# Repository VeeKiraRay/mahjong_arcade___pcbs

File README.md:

# Mahjong arcade DIY control panels
Kicad projects for a small mahjong control panel pcb that can be wired to be used with a real arcade game

Inspired by buffis JammaMahjongAdapter
https://github.com/buffis/JammaMahjongAdapter

Mahjong pinout that was followed when designing these

Comparison with different versions next to "Hot Gimmick 3" arcade pcb. Added a commercial version for Windows as a size comparison as well. 

Ready to play with small control panel and mahjong to jamma adapter

## Mahjong control panel symbols
For printing stickers or otherwise marking control panels here are some of the common characters to use

Lower part of control panel
- coin (F.F.) / ko-i-n / コイン
- start / su-ta-a-to / スタート 
- bet / be-t-to / ベット
- take score / te-i-ku-su-ko / テイクスコアー
- double up (WUP) / da-bu-ru a-p-pu / ダブルアップ  
- big / bi-g-gu / ビッグ
- small / su-mo-ru / スモール
- last chance / ra-su-to ch-a-n-su / ラストチャンス
- kan / ka-n / カン
- pon / po-n / ポン
- chi / ch-i / チー
- riichi / ri-i-chi / リーチ
- ron / ro-n / ロン

Character suite to number conversion
- 1 / 一
- 2 / 二
- 3 / 三
- 4 / 四
- 5 / 五
- 6 / 六
- 7 / 七
- 8 / 八
- 9 / 九

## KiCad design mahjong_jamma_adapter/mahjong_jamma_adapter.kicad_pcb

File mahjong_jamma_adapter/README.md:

# Mahjong to JAMMA adapter

Enables you to play Mahjong games in a JAMMA setup like arcade cabinet or supergun. 
This has 3.96mm pitch for the mahjong side pads which is same as with JAMMA. Note that some Mahjong games use 4mm pitch.
Be sure to check that the adapter lines with the game pcb pads correctly.

The main Mahjong controls can be extended with the 6- and 5-pin connectors. 
Additional 4-pin connector is also available for wiring coin, test and service buttons with GND.
Connector pins are with 2.5mm pitch, but 2.54mm should also work.

The -5V requirement and GND to "JAMMA Spk-" can be bridged if needed.

Audio section can be wired with a switch to change between connecting "JAMMA Spk-" to "Mahjong Spk-" or to GND.
Be sure what connections your game(s) require. For example Hot Gimmick needs the "JAMMA Spk-" to be connected to "Mahjong Spk-" or there won't be any sound.
Connecting this wrong can cause sound to be missing, distorted, low volume and possibly components overheating.

Mahjong pinout that was followed when designing this

Bare pcb

Control panel poulated

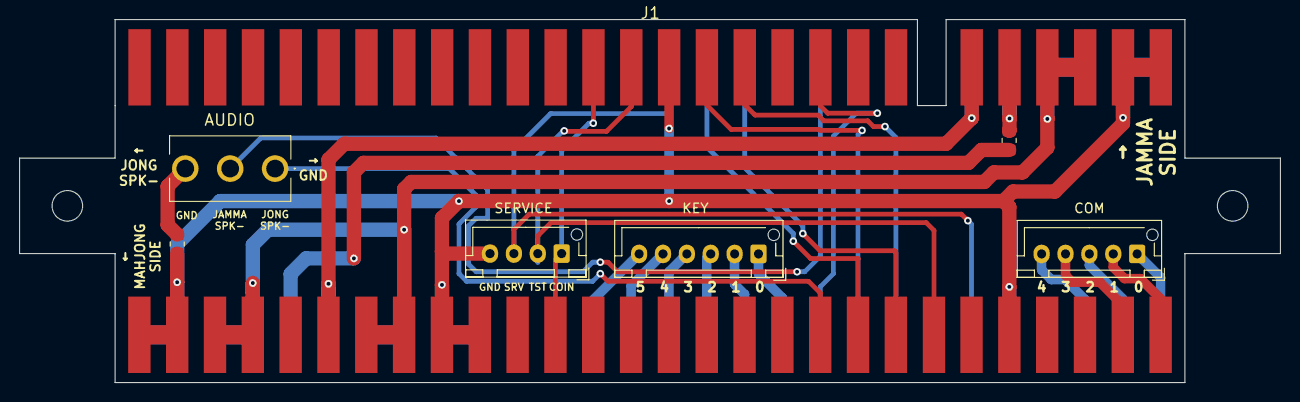
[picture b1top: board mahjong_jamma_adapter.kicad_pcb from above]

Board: 2 copper layers, 132.0 x 38.0 mm, 8 parts (0 on the bottom side), 27 nets.

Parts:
AUDIO: Mahjong_Connector; MAHJONG-56
COM: Conn_01x05; JST_XH_B5B-XH-AM_1x05_P2.50mm_Vertical
J1: Jamma_Connector; JAMMA-56
JMP1, JMP2: SolderJumper_2_Open; R_0805_2012Metric_Pad1.20x1.40mm_HandSolder
KEY: Conn_01x06; JST_XH_B6B-XH-AM_1x06_P2.50mm_Vertical
SERVICE: Conn_01x04; JST_XH_B4B-XH-AM_1x04_P2.50mm_Vertical
SW1: SW_SPDT; A101SYCQ04

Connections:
5V: AUDIO.21, AUDIO.22, AUDIO.25, AUDIO.26, AUDIO.Y, AUDIO.Z, AUDIO.c, AUDIO.d, J1.3, J1.4, J1.C, J1.D
12V: AUDIO.23, AUDIO.a, J1.6, J1.F
-5V: J1.5, J1.E, JMP1.2 (B)
-5V_M: AUDIO.b, JMP1.1 (A)
BLUE: AUDIO.K, J1.13
COIN: AUDIO.17, J1.16, SERVICE.1
COM0-3: AUDIO.A, COM.1
COM1-2: AUDIO.1, COM.2
COM2-6: AUDIO.B, COM.3
COM3-10: AUDIO.2, COM.4
COM4-7: AUDIO.C, COM.5
GND: AUDIO.5, AUDIO.19, AUDIO.20, AUDIO.27, AUDIO.28, AUDIO.E, AUDIO.W, AUDIO.X, AUDIO.e, AUDIO.f, J1.1, J1.2, J1.14, J1.A, J1.B, JMP2.2 (B), SERVICE.4
GREEN: AUDIO.8, J1.N
JAMMA_SPK-: J1.L, SW1.2 (B)
JONG_SPK-: AUDIO.10, SW1.1 (A)
KEY0-4: AUDIO.M, KEY.1
KEY1-5: AUDIO.N, KEY.2
KEY2-8: AUDIO.P, KEY.3
KEY3-9: AUDIO.R, KEY.4
KEY4-11: AUDIO.S, KEY.5
KEY5-1: AUDIO.T, KEY.6
unnamed: JMP2.1 (A), SW1.3 (C)
RED: AUDIO.J, J1.12
SERVICE: AUDIO.F, J1.R, SERVICE.3
SPK+: AUDIO.L, J1.10
SYNC: AUDIO.9, J1.P
TEST: AUDIO.7, J1.15, SERVICE.2

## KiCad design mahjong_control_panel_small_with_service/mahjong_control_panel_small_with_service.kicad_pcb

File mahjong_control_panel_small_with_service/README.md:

# Mahjong control panel small with service buttons

Smaller version of control panel with basic inputs and additional buttons for easy coin in, test for menus and service for alternative coin in and options.

- Connectors are with 2.5mm pitch, but 2.54mm should also work
- All buttons are 6mm. Any correct size button should work with or without the hats.
- Holes at the edge are M3 for attaching legs or to a case.

Bare pcb

Control panel poulated

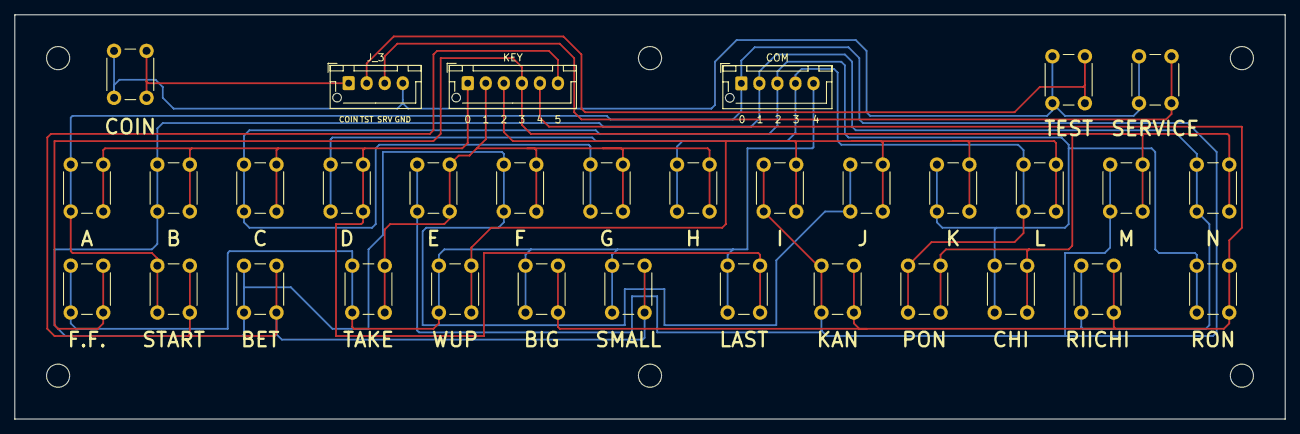
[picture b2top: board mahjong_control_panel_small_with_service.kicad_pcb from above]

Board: 2 copper layers, 176.0 x 56.0 mm, 33 parts (0 on the bottom side), 15 nets.

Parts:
A: SW_A; SW_PUSH_6mm_H7.3mm
B: SW_B; SW_PUSH_6mm_H7.3mm
BET: SW_BET; SW_PUSH_6mm_H7.3mm
BIG: SW_BIG; SW_PUSH_6mm_H7.3mm
C: SW_C; SW_PUSH_6mm_H7.3mm
CHI: SW_CHI; SW_PUSH_6mm_H7.3mm
COIN: SW_COIN; SW_PUSH_6mm_H7.3mm
COM: Conn_01x05; JST_XH_B5B-XH-AM_1x05_P2.50mm_Vertical
D: SW_D; SW_PUSH_6mm_H7.3mm
E: SW_E; SW_PUSH_6mm_H7.3mm
F: SW_F; SW_PUSH_6mm_H7.3mm
F.F.: SW_F.F.; SW_PUSH_6mm_H7.3mm
G: SW_G; SW_PUSH_6mm_H7.3mm
H: SW_H; SW_PUSH_6mm_H7.3mm
I: SW_I; SW_PUSH_6mm_H7.3mm
J: SW_J; SW_PUSH_6mm_H7.3mm
J_3: Conn_01x04; JST_XH_B4B-XH-AM_1x04_P2.50mm_Vertical
K: SW_K; SW_PUSH_6mm_H7.3mm
KAN: SW_KAN; SW_PUSH_6mm_H7.3mm
KEY: Conn_01x06; JST_XH_B6B-XH-AM_1x06_P2.50mm_Vertical
L: SW_L; SW_PUSH_6mm_H7.3mm
LAST: SW_LAST; SW_PUSH_6mm_H7.3mm
M: SW_M; SW_PUSH_6mm_H7.3mm
N: SW_N; SW_PUSH_6mm_H7.3mm
PON: SW_PON; SW_PUSH_6mm_H7.3mm
RIICHI: SW_REACH; SW_PUSH_6mm_H7.3mm
RON: SW_RON; SW_PUSH_6mm_H7.3mm
SERVICE: SW_SERVICE; SW_PUSH_6mm_H7.3mm
SMALL: SW_SMALL; SW_PUSH_6mm_H7.3mm
START: SW_START; SW_PUSH_6mm_H7.3mm
TAKE: SW_TAKE; SW_PUSH_6mm_H7.3mm
TEST: SW_TEST; SW_PUSH_6mm_H7.3mm
WUP: SW_WUP; SW_PUSH_6mm_H7.3mm

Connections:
COM0-3: A.1 (C), COM.1, E.1 (C), I.1 (C), KAN.1 (C), M.1 (C), START.1 (C)
COM1-2: B.1 (C), BET.1 (C), COM.2, F.1 (C), J.1 (C), N.1 (C), RIICHI.1 (C)
COM2-6: C.1 (C), CHI.1 (C), COM.3, G.1 (C), K.1 (C), RON.1 (C)
COM3-10: COM.4, D.1 (C), H.1 (C), L.1 (C), PON.1 (C)
COM4-7: BIG.1 (C), COM.5, F.F..1 (C), LAST.1 (C), SMALL.1 (C), TAKE.1 (C), WUP.1 (C)
Coin: COIN.2 (D), J_3.1
GND: COIN.1 (C), J_3.4, SERVICE.1 (C), TEST.1 (C)
KEY0-4: A.2 (D), B.2 (D), C.2 (D), D.2 (D), KEY.1, LAST.2 (D)
KEY1-5: E.2 (D), F.2 (D), G.2 (D), H.2 (D), KEY.2, TAKE.2 (D)
KEY2-8: I.2 (D), J.2 (D), K.2 (D), KEY.3, L.2 (D), WUP.2 (D)
KEY3-9: CHI.2 (D), F.F..2 (D), KEY.4, M.2 (D), N.2 (D), PON.2 (D)
KEY4-11: BIG.2 (D), KAN.2 (D), KEY.5, RIICHI.2 (D), RON.2 (D)
KEY5-1: BET.2 (D), KEY.6, SMALL.2 (D), START.2 (D)
Service: J_3.3, SERVICE.2 (D)
Test: J_3.2, TEST.2 (D)

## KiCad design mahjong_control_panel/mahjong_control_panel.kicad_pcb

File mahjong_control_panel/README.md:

# Mahjong control panel

Control panel with just the basic inputs

- Connectors are with 2.5mm pitch, but 2.54mm should also work
- Main buttons are 12mm buttons. Any correct size button should work with or without the hats.
- Holes at the edge are M3 for attaching legs or to a case.

Bare pcb

Control panel poulated

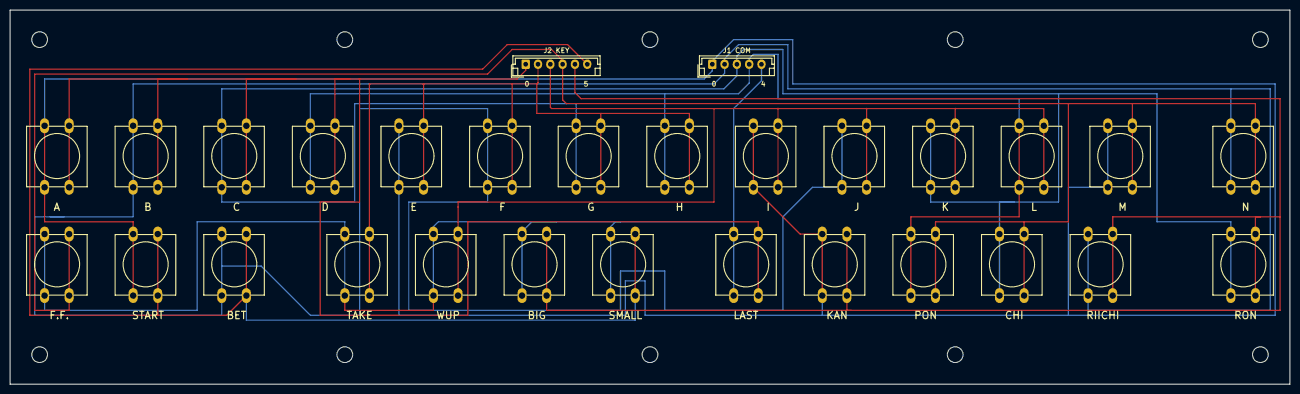
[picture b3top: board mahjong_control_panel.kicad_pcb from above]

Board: 2 copper layers, 260.0 x 76.0 mm, 29 parts (0 on the bottom side), 11 nets.

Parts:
A: SW_A; SW_PUSH-12mm
B: SW_B; SW_PUSH-12mm
BET: SW_BET; SW_PUSH-12mm
BIG: SW_BIG; SW_PUSH-12mm
C: SW_C; SW_PUSH-12mm
CHI: SW_CHI; SW_PUSH-12mm
D: SW_D; SW_PUSH-12mm
E: SW_E; SW_PUSH-12mm
F: SW_F; SW_PUSH-12mm
F.F.: SW_F.F.; SW_PUSH-12mm
G: SW_G; SW_PUSH-12mm
H: SW_H; SW_PUSH-12mm
I: SW_I; SW_PUSH-12mm
J: SW_J; SW_PUSH-12mm
J1 COM: Conn_01x05; JST_EH_B5B-EH-A_1x05_P2.50mm_Vertical
J2 KEY: Conn_01x06; JST_EH_B6B-EH-A_1x06_P2.50mm_Vertical
K: SW_K; SW_PUSH-12mm
KAN: SW_KAN; SW_PUSH-12mm
L: SW_L; SW_PUSH-12mm
LAST: SW_LAST; SW_PUSH-12mm
M: SW_M; SW_PUSH-12mm
N: SW_N; SW_PUSH-12mm
PON: SW_PON; SW_PUSH-12mm
RIICHI: SW_REACH; SW_PUSH-12mm
RON: SW_RON; SW_PUSH-12mm
SMALL: SW_SMALL; SW_PUSH-12mm
START: SW_START; SW_PUSH-12mm
TAKE: SW_TAKE; SW_PUSH-12mm
WUP: SW_WUP; SW_PUSH-12mm

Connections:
COM0-3: A.1 (C), E.1 (C), I.1 (C), J1 COM.1, KAN.1 (C), M.1 (C), START.1 (C)
COM1-2: B.1 (C), BET.1 (C), F.1 (C), J.1 (C), J1 COM.2, N.1 (C), RIICHI.1 (C)
COM2-6: C.1 (C), CHI.1 (C), G.1 (C), J1 COM.3, K.1 (C), RON.1 (C)
COM3-10: D.1 (C), H.1 (C), J1 COM.4, L.1 (C), PON.1 (C)
COM4-7: BIG.1 (C), F.F..1 (C), J1 COM.5, LAST.1 (C), SMALL.1 (C), TAKE.1 (C), WUP.1 (C)
KEY0-4: A.2 (D), B.2 (D), C.2 (D), D.2 (D), J2 KEY.1, LAST.2 (D)
KEY1-5: E.2 (D), F.2 (D), G.2 (D), H.2 (D), J2 KEY.2, TAKE.2 (D)
KEY2-8: I.2 (D), J.2 (D), J2 KEY.3, K.2 (D), L.2 (D), WUP.2 (D)
KEY3-9: CHI.2 (D), F.F..2 (D), J2 KEY.4, M.2 (D), N.2 (D), PON.2 (D)
KEY4-11: BIG.2 (D), J2 KEY.5, KAN.2 (D), RIICHI.2 (D), RON.2 (D)
KEY5-1: BET.2 (D), J2 KEY.6, SMALL.2 (D), START.2 (D)

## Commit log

2022-12-29 Initial commit for projects
2022-12-29 Add README and images
2022-12-29 Refactor folder names and improve README
2022-12-30 Improve README.md layout
2022-12-30 Add mahjong to jamma adapter
2022-12-30 Improve README.md
